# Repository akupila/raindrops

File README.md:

raindrops
=========

Arduino based project for rain prediction installation

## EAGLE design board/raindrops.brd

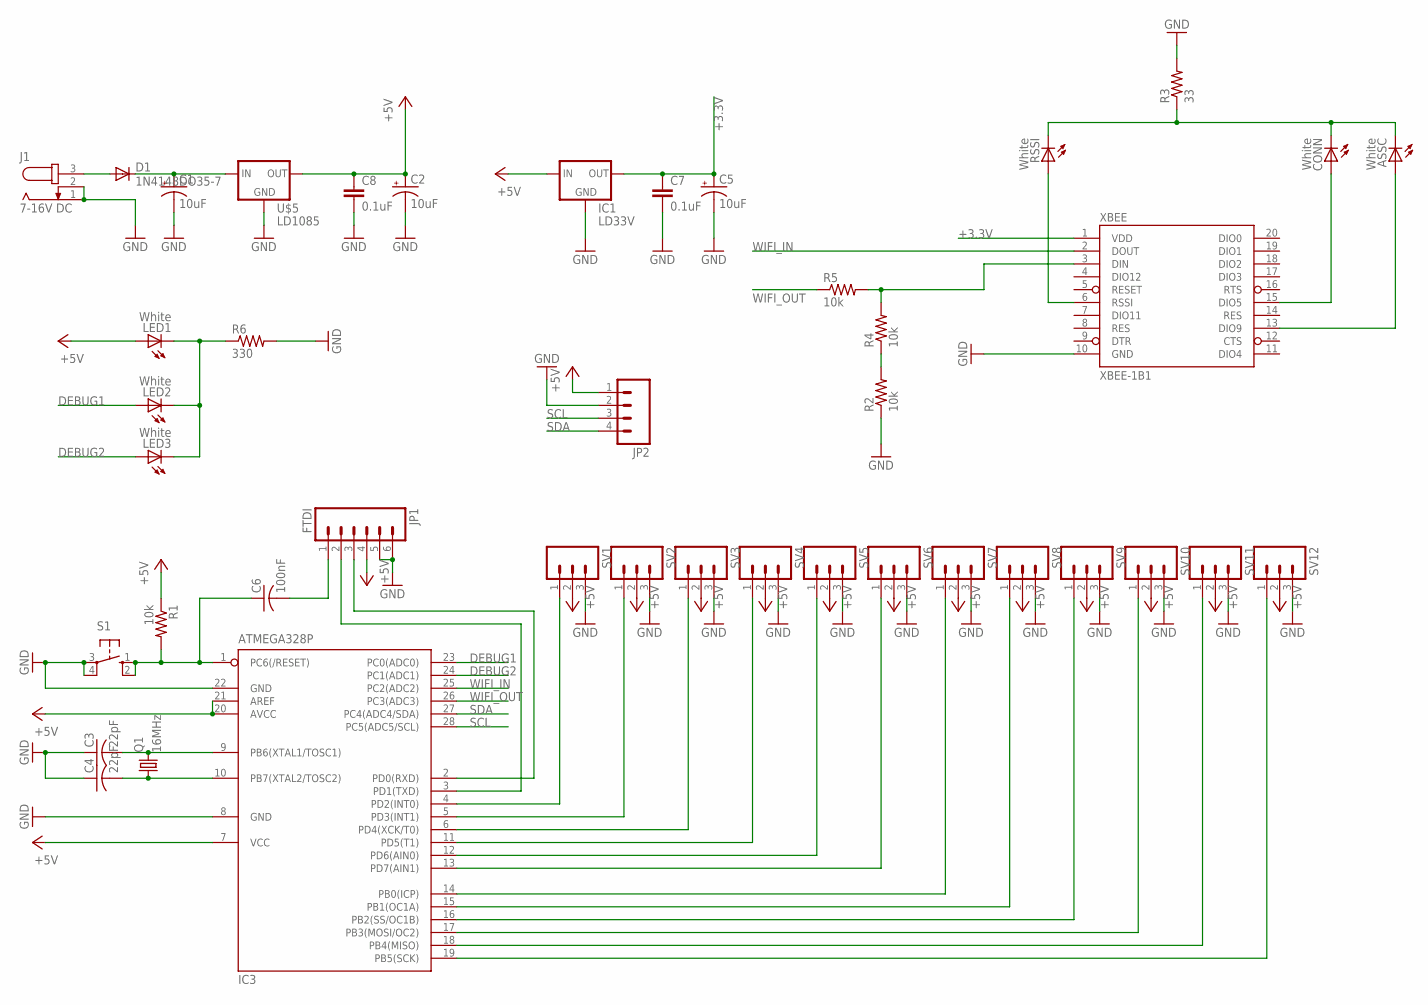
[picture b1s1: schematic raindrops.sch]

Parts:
ASSC: White; CHIPLED_0603
C1, C2, C5: 10uF; CPOL-RADIAL-10UF-25V
C3, C4: 22pF; C025-025X050
C6: 100nF; C025-025X050
C7, C8: 0.1uF; 0402-CAP
CONN: White; CHIPLED_0603
D1: 1N4148DO35-7; DO35-7
IC1: LD33V; 78XXL
IC3: ATMEGA328P; DIL28-3
J1: 7-16V DC; SPC4077
JP1: FTDI; 1X06
JP2: M04PTH; 1X04
LED1, LED2, LED3: White; CHIPLED_0603
Q1: 16MHz; HC49/S
R1, R2, R4, R5: 10k; 0603-RES
R3: 33; AXIAL-0.3
R6: 330; AXIAL-0.3
RSSI: White; CHIPLED_0603
S1: 10-XX; B3F-10XX
SV1, SV2, SV3, SV4, SV5, SV6, SV7, SV8, SV9, SV10, SV11, SV12: M03PTH; 1X03
U$5: LD1085; 78XXL
XBEE: XBEE-1B1; XBEE-1

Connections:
+3.3V: C5.1 (+), C7.1, IC1.GND (OUT), XBEE.1 (VDD)
+5V: C2.1 (+), C8.1, IC1.OUT (IN), IC3.7 (VCC), IC3.20 (AVCC), IC3.21 (AREF), JP1.4, JP2.1, LED1.A, R1.1, SV1.2, SV2.2, SV3.2, SV4.2, SV5.2, SV6.2, SV7.2, SV8.2, SV9.2, SV10.2, SV11.2, SV12.2, U$5.GND (OUT)
ASSC: ASSC.A, XBEE.13 (DIO9)
CONN: CONN.A, XBEE.15 (DIO5)
CONN1: IC3.4 (PD2(INT0)), SV1.1
CONN2: IC3.5 (PD3(INT1)), SV2.1
CONN3: IC3.6 (PD4(XCK/T0)), SV3.1
CONN4: IC3.11 (PD5(T1)), SV4.1
CONN5: IC3.12 (PD6(AIN0)), SV5.1
CONN6: IC3.13 (PD7(AIN1)), SV6.1
CONN7: IC3.14 (PB0(ICP)), SV7.1
CONN8: IC3.15 (PB1(OC1A)), SV8.1
CONN9: IC3.16 (PB2(SS/OC1B)), SV9.1
CONN10: IC3.17 (PB3(MOSI/OC2)), SV10.1
CONN11: IC3.18 (PB4(MISO)), SV11.1
CONN12: IC3.19 (PB5(SCK)), SV12.1
DEBUG1: IC3.23 (PC0(ADC0)), LED2.A
DEBUG2: IC3.24 (PC1(ADC1)), LED3.A
GND: C1.2 (-), C2.2 (-), C3.1, C4.1, C5.2 (-), C7.2, C8.2, IC1.IN (GND), IC3.8 (GND), IC3.22 (GND), J1.1, J1.2, JP1.5, JP1.6, JP2.2, R2.1, R3.P$2 (2), R6.P$2 (2), S1.3, S1.4 (P1), SV1.3, SV2.3, SV3.3, SV4.3, SV5.3, SV6.3, SV7.3, SV8.3, SV9.3, SV10.3, SV11.3, SV12.3, U$5.IN (GND), XBEE.10 (GND)
LED-RESISTOR: LED1.C, LED2.C, LED3.C, R6.P$1 (1)
unnamed: C6.2, JP1.1
RESET: C6.1, IC3.1 (PC6(/RESET)), R1.2, S1.1 (S), S1.2 (S1)
RSSI: RSSI.A, XBEE.6 (RSSI)
RXO: IC3.2 (PD0(RXD)), JP1.3
SCL: IC3.28 (PC5(ADC5/SCL)), JP2.3
SDA: IC3.27 (PC4(ADC4/SDA)), JP2.4
TXO: IC3.3 (PD1(TXD)), JP1.2
V-DIV: R2.2, R4.1
VIN-POST-DIODE: C1.1 (+), D1.C, U$5.OUT (IN)
VIN-PRE-DIODE: D1.A, J1.3
WIFI_IN: IC3.25 (PC2(ADC2)), XBEE.2 (DOUT)
WIFI_OUT: IC3.26 (PC3(ADC3)), R5.1
XBEE-DIN: R4.2, R5.2, XBEE.3 (DIN)
XBEE-LED-RESISTOR: ASSC.C, CONN.C, R3.P$1 (1), RSSI.C
XTAL1: C3.2, IC3.9 (PB6(XTAL1/TOSC1)), Q1.2
XTAL2: C4.2, IC3.10 (PB7(XTAL2/TOSC2)), Q1.1

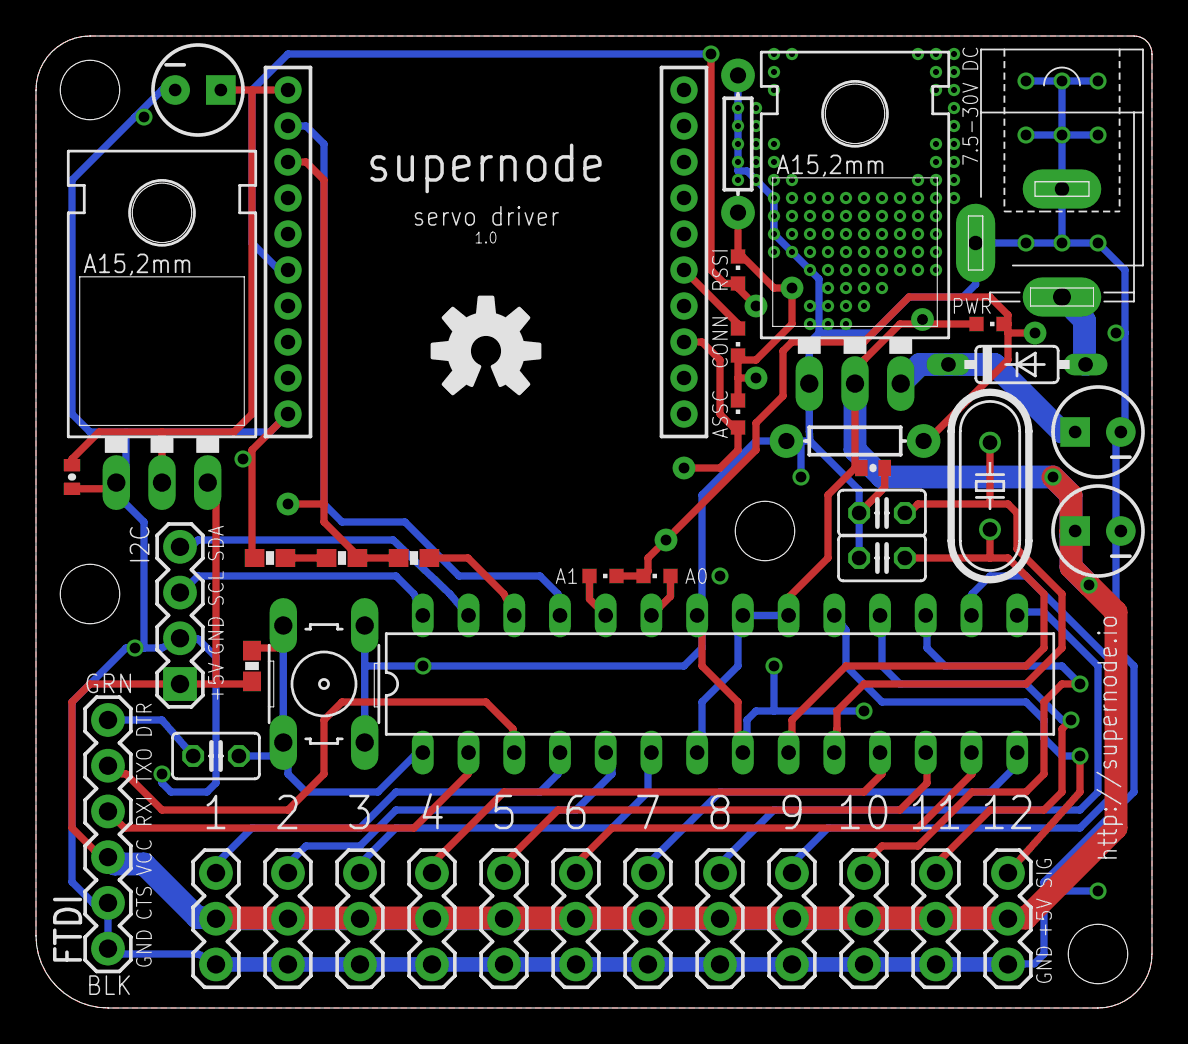
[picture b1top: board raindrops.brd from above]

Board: 2 copper layers, 62.0 x 54.0 mm, 46 parts (0 on the bottom side), 36 nets.

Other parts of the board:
U$1, U$2, U$3, U$4: STAND-OFF

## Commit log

2013-01-15 Added schematic and board design
2013-01-15 Using static location (Amsterdam) for more rain than server's location (CA) ;)
2013-01-15 Starting calibration tests. Added echo for unrecognized commands for testing
2013-01-16 Allow | as an incoming character
2013-01-16 Fixing previous commit
2013-01-16 Calibration WIP
2013-01-21 Allowing < and >
2013-01-23 Using another ATMEGA over I2C for sensing positions (using buttons or reed switches)
2013-01-23 Moved to ContinuousServo library
2013-01-23 Using I2C to read in rotational values from another uC

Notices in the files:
parts and their libraries:
SparkFun-Resistors: Licensing: CC v3.0 Share-Alike You are welcome to use this library for commercial purposes.
